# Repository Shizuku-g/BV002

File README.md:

# BV001

Design by nerdqaxeplus2(https://github.com/shufps/qaxe), change the ASIC to 1 x BM1373 AA (6.1TH/s SHA256)

Design tested and validated.  
Consume about 110 Watts on 12V for about 6.1TH/s (Vcore 1250mV, frequency 900Hz).  
Run at 735 MHz and 1140 mV, power wall around 78W, efficiency 14J/Th, 5TH/s.  
Use a 12V 15A PSU.

---

# BV002

**It is still an untested prototype! Don't build this expecting it to work at all.**

---

# BV003

**It is still an untested prototype! Don't build this expecting it to work at all.**

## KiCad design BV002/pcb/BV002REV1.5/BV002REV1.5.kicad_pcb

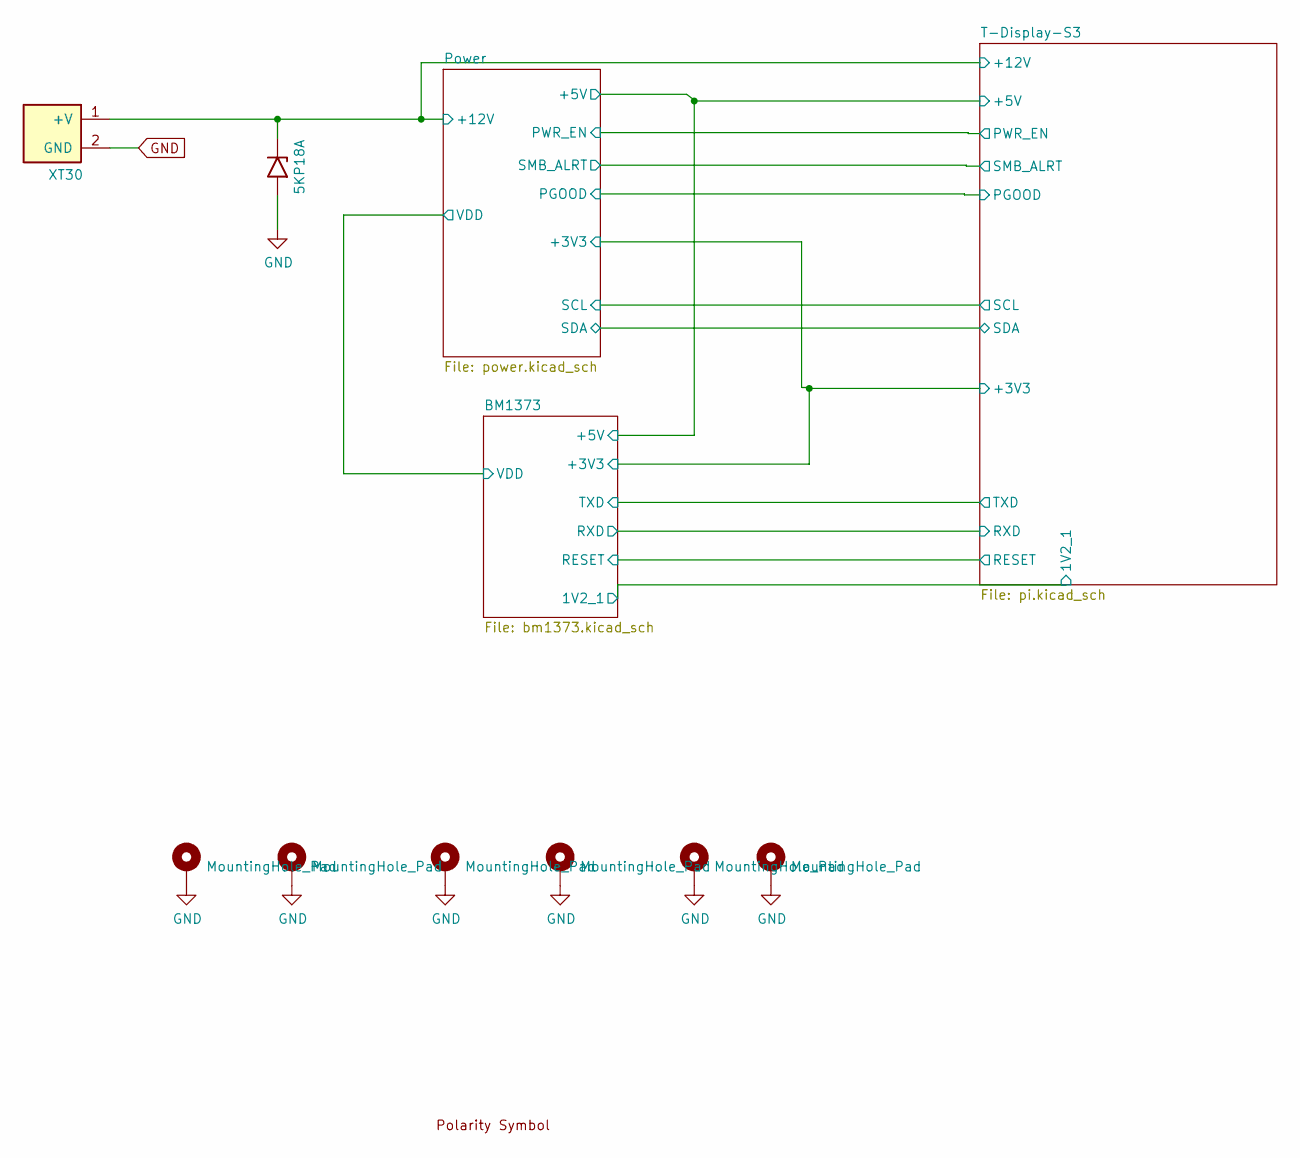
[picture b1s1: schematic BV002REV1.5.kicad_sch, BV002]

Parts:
D1: 5KP18A; D_SMB; PARTNO SMBJ12A; LCSC C3001973
H1, H2, H3, H4, H5, H6: MountingHole_Pad; MountingHole_3.2mm_M3_Pad_Via
J1: XT30; XT30PW-M; PARTNO XT30PW-M; LCSC C431092
U1: polarity

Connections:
+12V: D1.1 (A1), J1.1 (+V); also elsewhere on the board

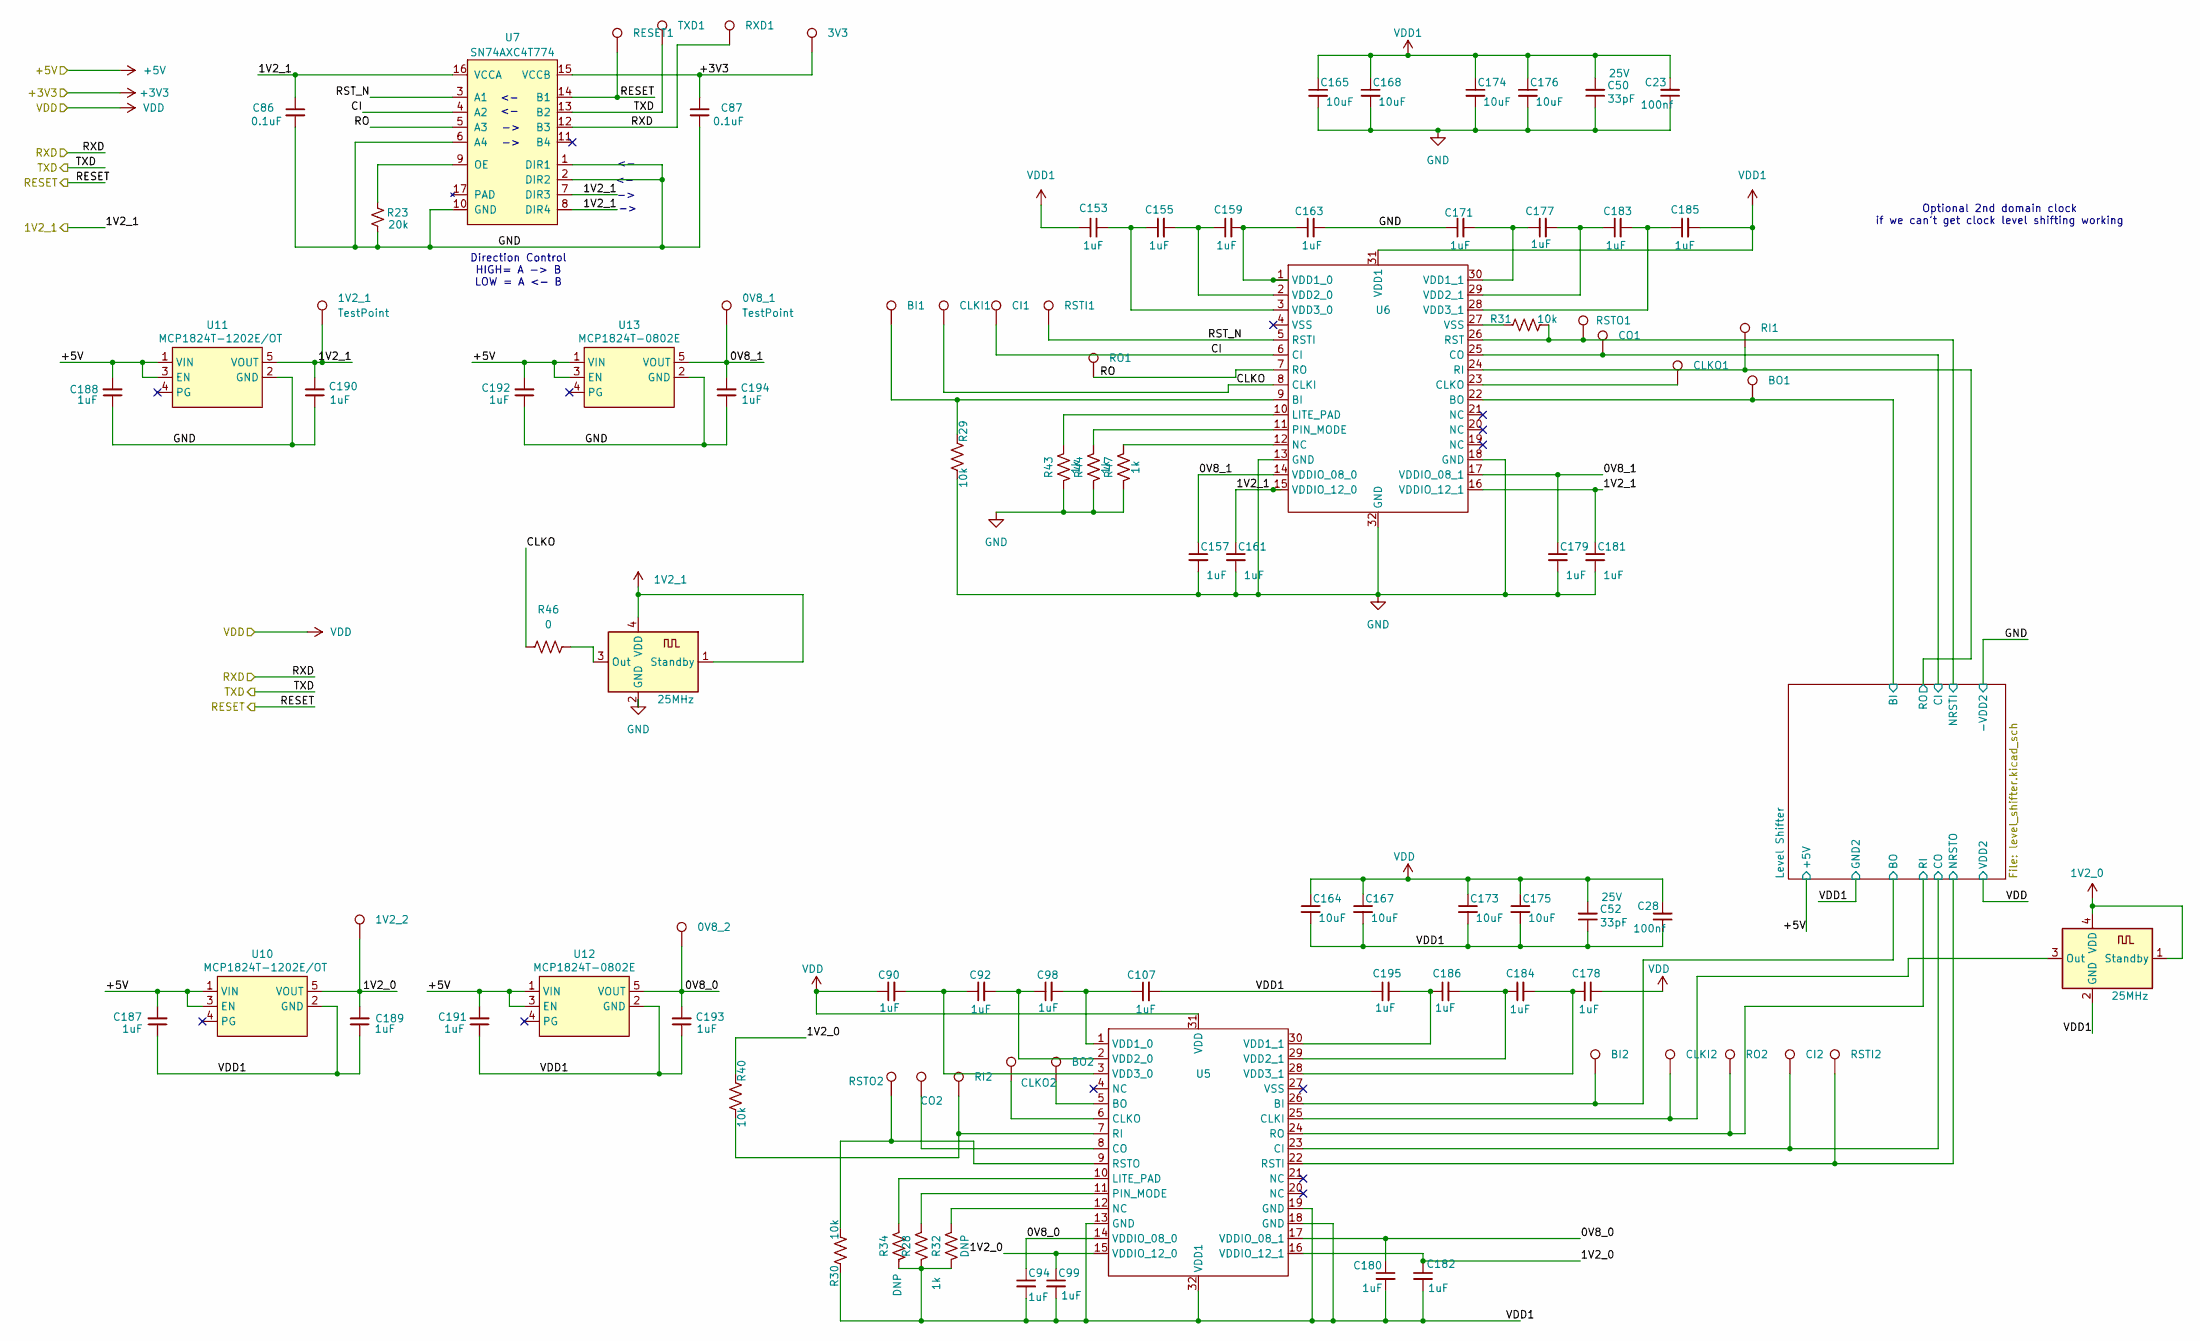
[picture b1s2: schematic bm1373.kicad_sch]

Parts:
0V8_1, 1V2_1: TestPoint; TestPoint_Pad_D1.5mm
0V8_2, 1V2_2, 3V3: TestPoint_Pad_D1.5mm
BI1, BI2: TestPoint_Pad_D1.5mm
BO1, BO2: TestPoint_Pad_D1.5mm
C23, C28: 100nf; C_0402_1005Metric; PARTNO GRM188R61E106KA73D
C50, C52: 33pF; C_0402_1005Metric; Voltage 25V; PARTNO KGM05ACG1E330JH
C86, C87: 0.1uF; C_0402_1005Metric; PARTNO KGM05AR71C104KH
C90, C92, C94, C98, C99, C107, C153, C155, C157, C159, C161, C163, C171, C177, C178, C179, C180, C181, C182, C183, C184, C185, C186, C195: 1uF; C_0402_1005Metric; PARTNO CL05A105KO5NNNC; LCSC C29266
C164, C165, C167, C168, C173, C174, C175, C176: 10uF; C_0603_1608Metric; PARTNO CL10A106MO8NQNC; LCSC C92487 Hot
C187, C188, C189, C190, C191, C192, C193, C194: 1uF; C_0402_1005Metric; PARTNO EMK105BJ105MV-F
CI1, CI2: TestPoint_Pad_D1.5mm
CLKI1, CLKI2: TestPoint_Pad_D1.5mm
CLKO1, CLKO2: TestPoint_Pad_D1.5mm
CO1, CO2: TestPoint_Pad_D1.5mm
R23: 20k; R_0402_1005Metric; PARTNO RC0402FR-0720KL
R28, R43, R44, R47: 1k; R_0402_1005Metric; PARTNO RC0402FR-071KL; LCSC C106235
R29, R30, R31, R40: 10k; R_0402_1005Metric; PARTNO RC0402DR-0710KL; LCSC C471764
R32, R34: DNP; R_0402_1005Metric; PARTNO RC0402FR-071KL; LCSC C106235
R46: 0; R_0402_1005Metric; PARTNO RC0402JR-070RL
RESET1: TestPoint_Pad_D1.5mm
RI1, RI2: TestPoint_Pad_D1.5mm
RO1, RO2: TestPoint_Pad_D1.5mm
RSTI1, RSTI2: TestPoint_Pad_D1.5mm
RSTO1, RSTO2: TestPoint_Pad_D1.5mm
RXD1: TestPoint_Pad_D1.5mm
TXD1: TestPoint_Pad_D1.5mm
U5, U6: B1373CC
U7: SN74AXC4T774; TSSOP-16_4.4x5mm_P0.65mm; PARTNO SN74AXC4T774BQBR
U8, U9: 25MHz; Oscillator_SMD_EuroQuartz_XO32-4Pin_3.2x2.5mm; PARTNO SX3M25.000E20F30THN
U10, U11: MCP1824T-1202E/OT; SOT-23-5; PARTNO MCP1824T-1202E/OT
U12, U13: MCP1824T-0802E; SOT-23-5; PARTNO MCP1824T-0802E/OT

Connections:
1V2_0: 1V2_2.1, C99.1, C182.1, C189.2, R40.1, U5.15 (VDDIO_12_0), U5.16 (VDDIO_12_1), U8.1 (Standby), U8.4 (VDD), U10.5 (VOUT)
1V2_1: 1V2_1.1, C86.1, C161.1, C181.1, C190.2, U6.15 (VDDIO_12_0), U6.16 (VDDIO_12_1), U7.7 (DIR3), U7.8 (DIR4), U7.16 (VCCA), U9.1 (Standby), U9.4 (VDD), U11.5 (VOUT); also elsewhere on the board
+5V: C187.2, C188.2, C191.2, C192.2, U10.1 (VIN), U10.3 (EN), U11.1 (VIN), U11.3 (EN), U12.1 (VIN), U12.3 (EN), U13.1 (VIN), U13.3 (EN); also elsewhere on the board
/BM1373/0V8_0: 0V8_2.1, C94.1, C180.1, C193.2, U5.14 (VDDIO_08_0), U5.17 (VDDIO_08_1), U12.5 (VOUT)
/BM1373/0V8_1: 0V8_1.1, C157.1, C179.1, C194.2, U6.14 (VDDIO_08_0), U6.17 (VDDIO_08_1), U13.5 (VOUT)
/BM1373/CI: CI1.1 (1_1), U6.6 (CI), U7.4 (A2)
/BM1373/CLKO: CLKI1.1 (1_1), R46.1, U6.8 (CLKI)
/BM1373/Level Shifter/BI: BO1.1 (1_1), U6.22 (BO); also elsewhere on the board
/BM1373/Level Shifter/BI2: BI2.1 (1_1), U5.26 (BI); also elsewhere on the board
/BM1373/Level Shifter/CI: CO1.1 (1_1), U6.25 (CO); also elsewhere on the board
/BM1373/Level Shifter/CI2: CI2.1 (1_1), U5.23 (CI); also elsewhere on the board
/BM1373/Level Shifter/NRSTI: R31.2, RSTO1.1 (1_1), U6.26 (RST); also elsewhere on the board
/BM1373/Level Shifter/NRSTI2: RSTI2.1 (1_1), U5.22 (RSTI); also elsewhere on the board
/BM1373/Level Shifter/RO: RI1.1 (1_1), U6.24 (RI); also elsewhere on the board
/BM1373/Level Shifter/RO2: RO2.1 (1_1), U5.24 (RO); also elsewhere on the board
/BM1373/RESET: RESET1.1 (1_1), U7.14 (B1); also elsewhere on the board
/BM1373/RO: RO1.1 (1_1), U6.7 (RO), U7.5 (A3)
/BM1373/RST_N: RSTI1.1 (1_1), U6.5 (RSTI), U7.3 (A1)
/BM1373/RXD: RXD1.1 (1_1), U7.12 (B3); also elsewhere on the board
/BM1373/TXD: TXD1.1 (1_1), U7.13 (B2); also elsewhere on the board
unnamed: R31.1, U6.27 (VSS)
unnamed: R32.1, U5.12 (NC)
unnamed: R47.1, U6.12 (NC)
unnamed: BO2.1 (1_1), U5.5 (BO)
unnamed: CLKI2.1 (1_1), U5.25 (CLKI), U8.3 (Out)
unnamed: CLKO2.1 (1_1), U5.6 (CLKO)
unnamed: CO2.1 (1_1), U5.8 (CO)
unnamed: R34.1, U5.10 (LITE_PAD)
unnamed: R28.1, U5.11 (PIN_MODE)
unnamed: R40.2, RI2.1 (1_1), U5.7 (RI)
unnamed: R30.2, RSTO2.1 (1_1), U5.9 (RSTO)
unnamed: C98.2, C107.1, U5.1 (VDD1_0)
unnamed: C186.1, C195.2, U5.30 (VDD1_1)
unnamed: C92.2, C98.1, U5.2 (VDD2_0)
unnamed: C184.1, C186.2, U5.29 (VDD2_1)
unnamed: C90.2, C92.1, U5.3 (VDD3_0)
unnamed: C178.1, C184.2, U5.28 (VDD3_1)
unnamed: BI1.1 (1_1), R29.1, U6.9 (BI)
unnamed: CLKO1.1 (1_1), U6.23 (CLKO)
unnamed: R43.1, U6.10 (LITE_PAD)
unnamed: R44.1, U6.11 (PIN_MODE)
unnamed: C159.2, C163.1, U6.1 (VDD1_0)
unnamed: C171.2, C177.1, U6.30 (VDD1_1)
unnamed: C155.2, C159.1, U6.2 (VDD2_0)
unnamed: C177.2, C183.1, U6.29 (VDD2_1)
unnamed: C153.2, C155.1, U6.3 (VDD3_0)
unnamed: C183.2, C185.1, U6.28 (VDD3_1)
unnamed: R23.2, U7.9 (OE)
unnamed: R46.2, U9.3 (Out)
VDD: C28.2, C52.2, C90.1, C164.1, C167.1, C173.1, C175.1, C178.2, U5.31 (VDD); also elsewhere on the board
VDD1: C23.2, C28.1, C50.2, C52.1, C94.2, C99.2, C107.2, C153.1, C164.2, C165.1, C167.2, C168.1, C173.2, C174.1, C175.2, C176.1, C180.2, C182.2, C185.2, C187.1, C189.1, C191.1, C193.1, C195.1, R28.2, R30.1, R32.2, R34.2, U5.13 (GND), U5.18 (GND), U5.19 (GND), U5.32 (VDD1), U6.31 (VDD1), U8.2 (GND), U10.2 (GND), U12.2 (GND); also elsewhere on the board

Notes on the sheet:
Optional 2nd domain clock if we can't get clock level shifting working
Direction Control HIGH= A -> B LOW = A <- B

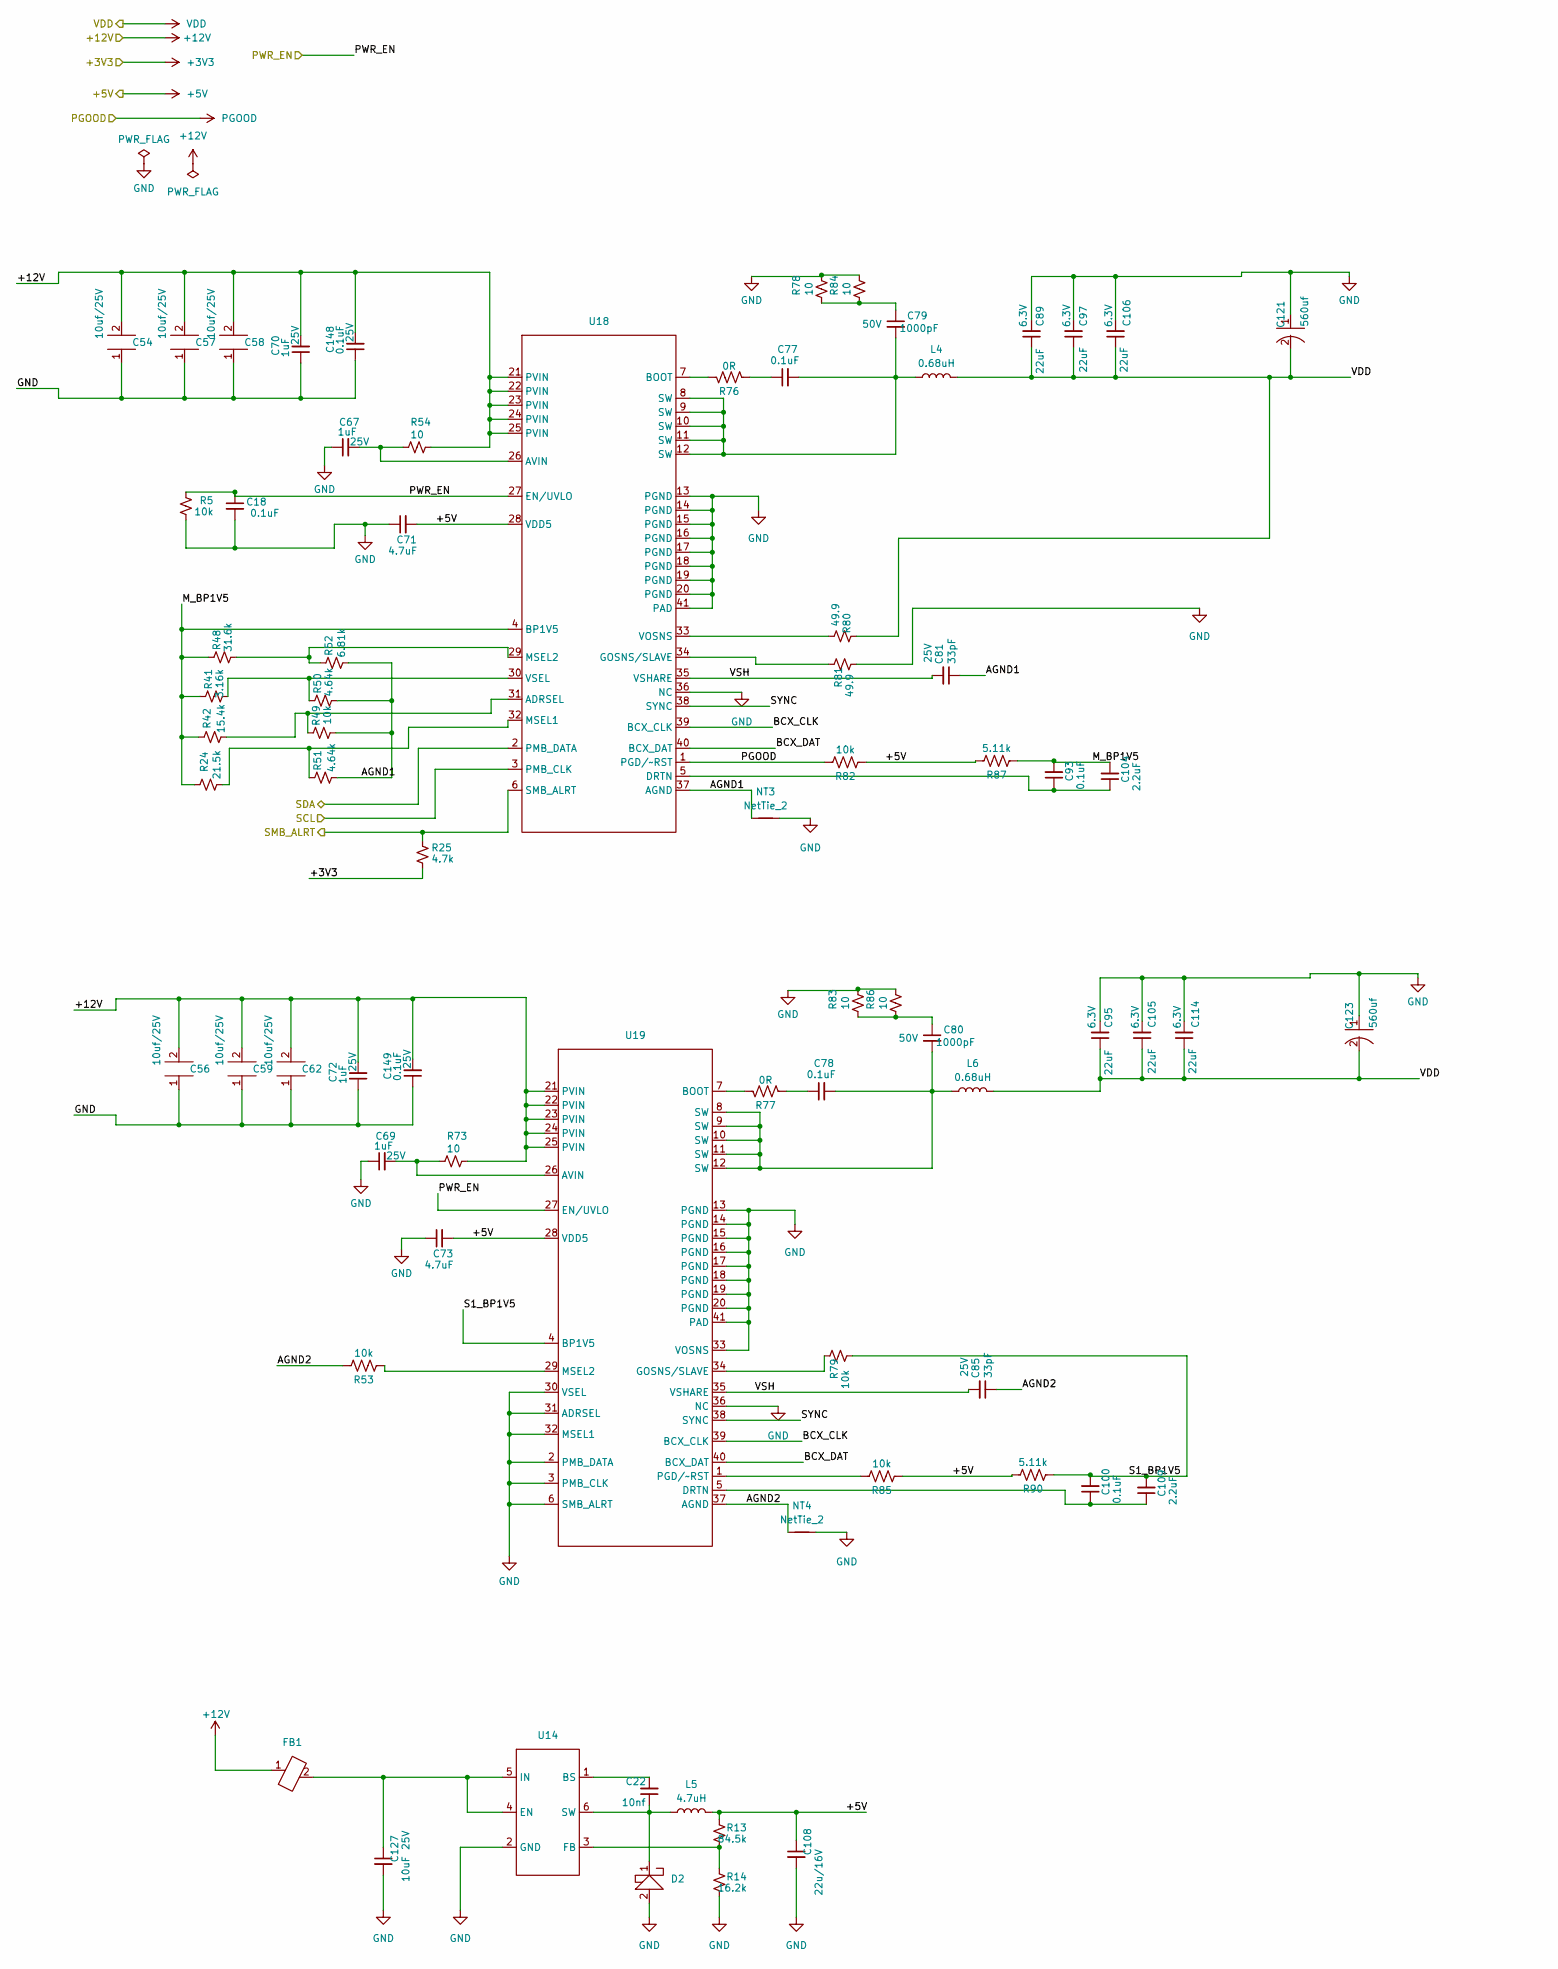
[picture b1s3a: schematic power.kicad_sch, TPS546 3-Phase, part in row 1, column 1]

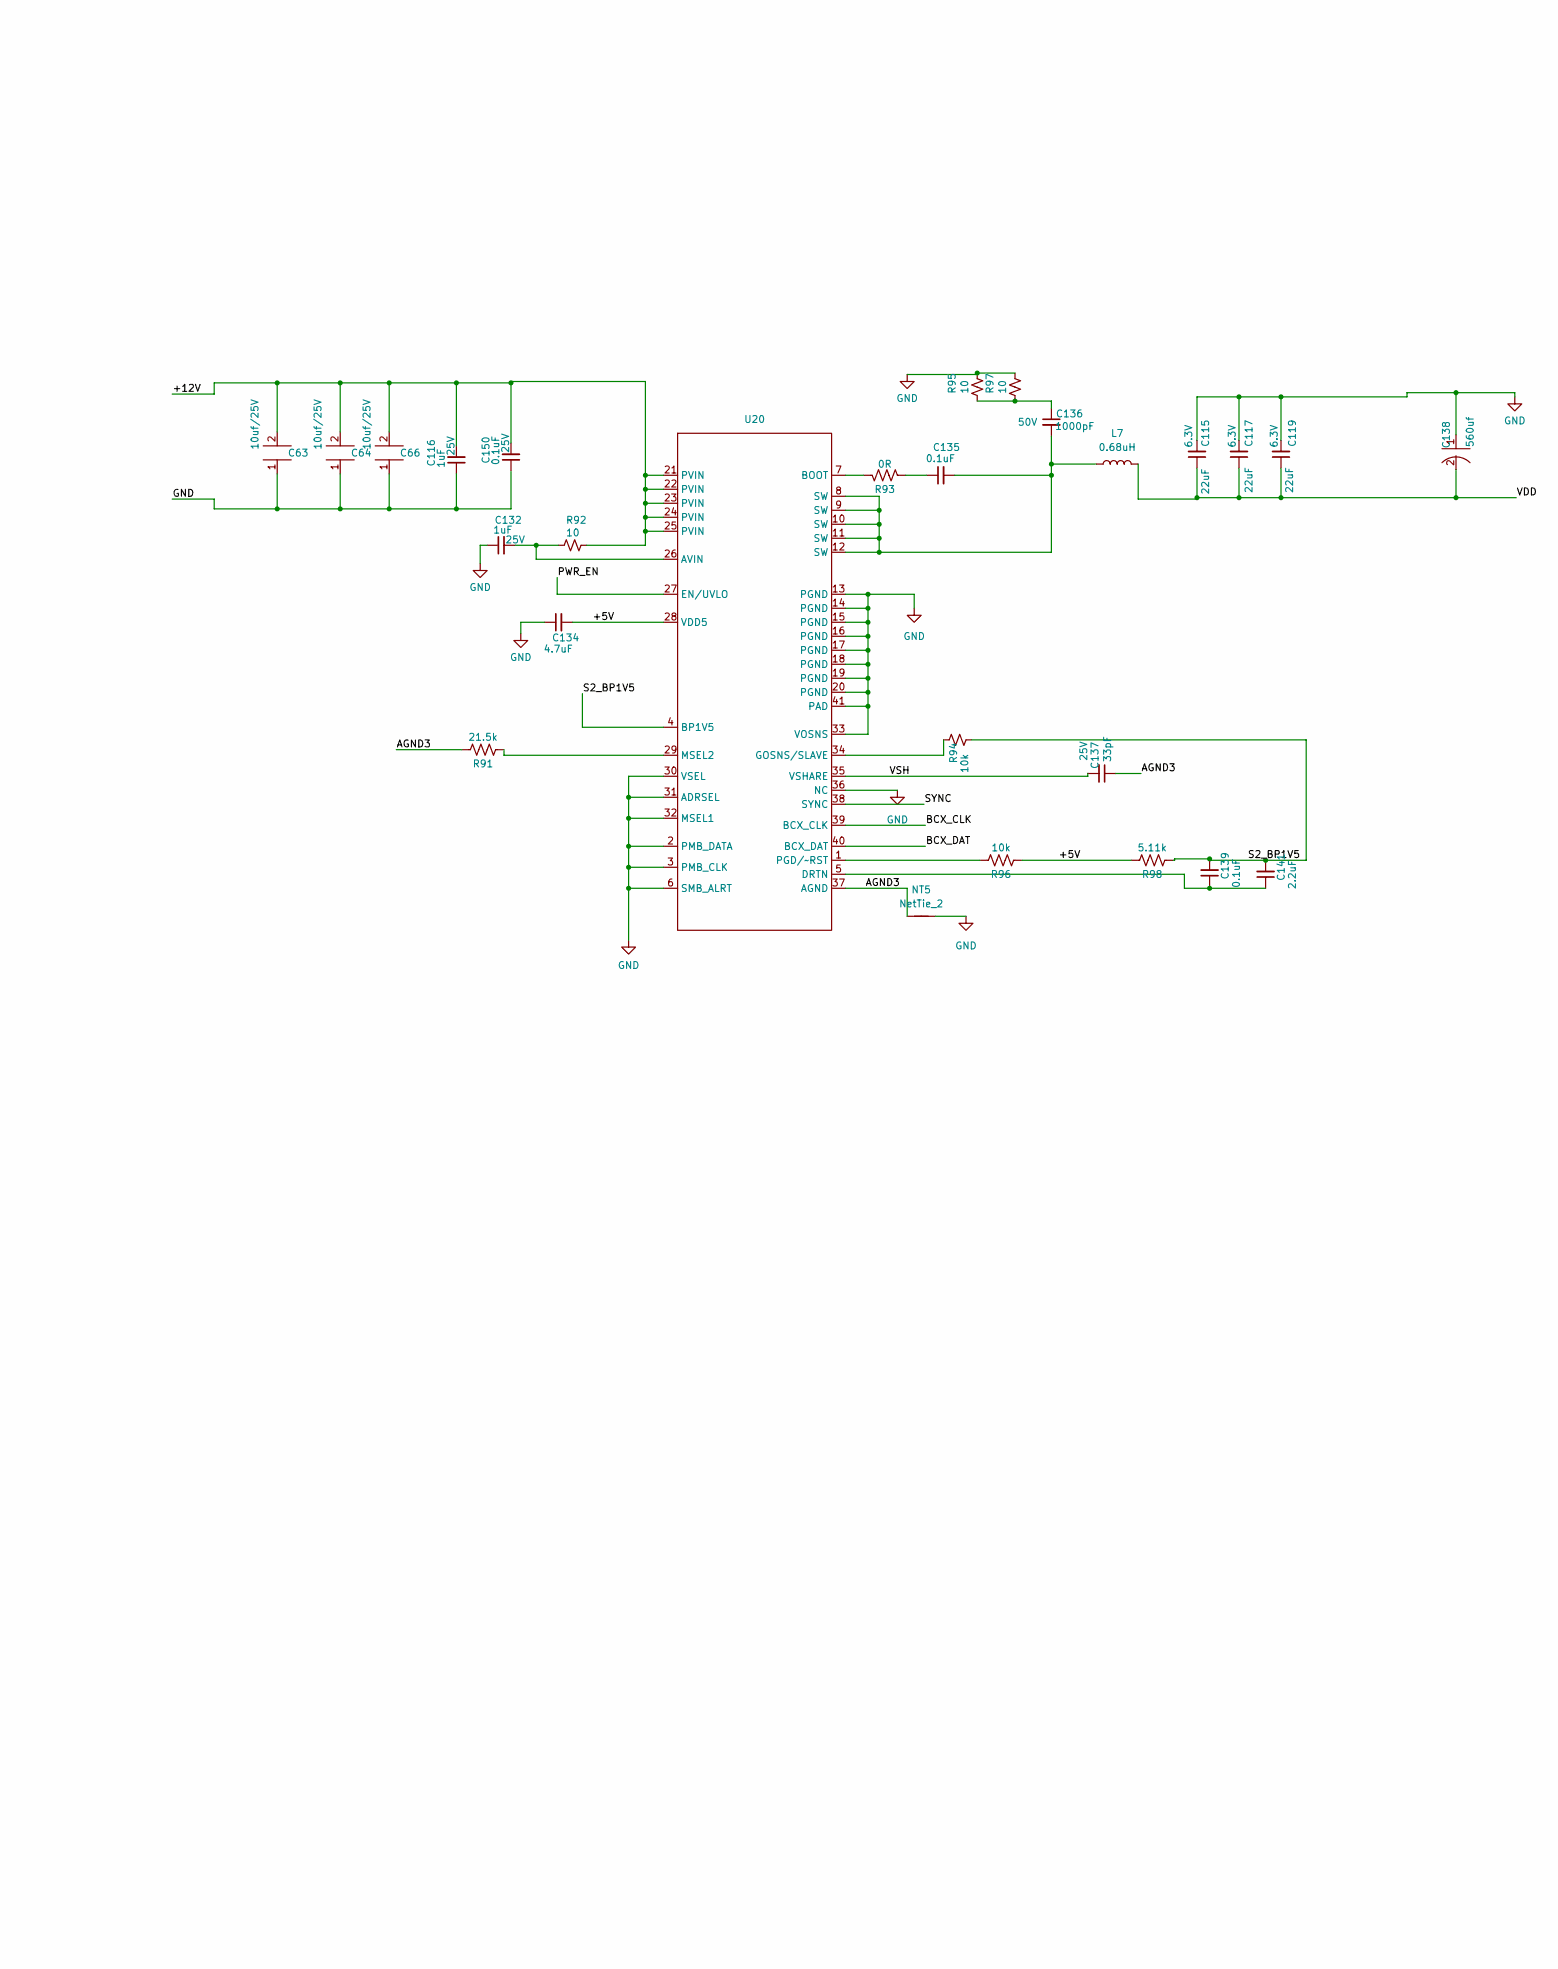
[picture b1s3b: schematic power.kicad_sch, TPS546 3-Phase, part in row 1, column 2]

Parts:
C18, C77, C78, C135: 0.1uF; C_0402_1005Metric; PARTNO KGM05AR71C104KH
C22: 10nf; C_0402_1005Metric; PARTNO GRM188R61E106KA73D
C54, C56, C57, C58, C59, C62, C63, C64, C66: 10uf/25V; C_0805_2012Metric
C67, C69, C70, C72, C116, C132: 1uF; C_0402_1005Metric; Voltage 25V; PARTNO TMK107B7105KA-T
C71, C73, C134: 4.7uF; C_0402_1005Metric; PARTNO GRM155R61A475MEAAD
C79, C80, C136: 1000pF; C_0402_1005Metric; Voltage 50V; PARTNO CC0402JRNPO9BN101
C81, C85, C137: 33pF; C_0402_1005Metric; Voltage 25V; PARTNO KGM05ACG1E330JH
C89, C95, C97, C105, C106, C114, C115, C117, C119: 22uF; C_1206_3216Metric; Voltage 6.3V; PARTNO CL31A107MQHNNNE
C93, C100, C139: 0.1uF; C_0402_1005Metric; PARTNO GRM155R61A475MEAAD
C104, C109, C141: 2.2uF; C_0402_1005Metric; PARTNO GRM155R61A475MEAAD
C108: 22u/16V; C_0603_1608Metric; PARTNO GRM188R61E106KA73D
C121, C123, C138: 560uf; D7.3xL4.3
C127: 10uF; C_0603_1608Metric; Voltage 25V; PARTNO GRM188R61E106KA73D
C148, C149, C150: 0.1uF; C_0402_1005Metric; Voltage 25V; PARTNO TMK107B7105KA-T
D2: D_SOD-128
FB1: FB0603
L4, L6, L7: 0.68uH; SLC1175-271MEC_COC; PARTNO SLC1175-301
L5: 4.7uH; L_Ferrocore_DLG-0703; PARTNO FTC201612S1R5MBCA
NT3, NT4, NT5: NetTie_2; NetTie-2_SMD_Pad0.2mmx1mm
R5, R49: 10k; R_0402_1005Metric; PARTNO RC0402JR-0710KL
R13: 84.5k; R_0402_1005Metric; PARTNO RC0402FR-0752K3L
R14: 16.2k; R_0402_1005Metric; PARTNO RC0402FR-0752K3L
R24: 21.5k; R_0402_1005Metric; PARTNO RC0402JR-0710KL
R25: 4.7k; R_0402_1005Metric; PARTNO RC0402JR-074K7L
R41: 3.16k; R_0402_1005Metric; PARTNO RC0402JR-0710KL
R42: 15.4k; R_0402_1005Metric; PARTNO RC0402JR-0710KL
R48: 31.6k; R_0402_1005Metric; PARTNO RC0402JR-0710KL
R50, R51: 4.64k; R_0402_1005Metric; PARTNO RC0402JR-0710KL
R52: 6.81k; R_0402_1005Metric; PARTNO RC0402JR-0710KL
R53, R82, R85, R96: 10k; R_0402_1005Metric; PARTNO RC0402DR-0710KL; LCSC C471764
R54, R73, R78, R83, R84, R86, R92, R95, R97: 10; R_0402_1005Metric; PARTNO RC0402FR-0710RL
R76, R77, R93: 0R; R_0402_1005Metric; PARTNO RC0402FR-071KL; LCSC C106235
R79, R94: 10k; R_0402_1005Metric; PARTNO RC0402FR-0749R9L
R80, R81: 49.9; R_0402_1005Metric; PARTNO RC0402FR-0749R9L
R87, R90, R98: 5.11k; R_0402_1005Metric; PARTNO RC0402DR-0710KL; LCSC C471764
R91: 21.5k; R_0402_1005Metric; PARTNO RC0402DR-0710KL; LCSC C471764
U14: SOT-23-6
U18, U19, U20: LQFN40-CLIP

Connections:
+5V: C71.2, C73.2, C108.1, C134.2, L5.2, R13.2, R82.1, R85.1, R87.2, R90.2, R96.1, R98.2, U18.28 (VDD5), U19.28 (VDD5), U20.28 (VDD5); also elsewhere on the board
+12V: C54.2, C56.2, C57.2, C58.2, C59.2, C62.2, C63.2, C64.2, C66.2, C70.2, C72.2, C116.2, C148.2, C149.2, C150.2, FB1.1, R54.1, R73.1, R92.1, U18.21 (PVIN), U18.22 (PVIN), U18.23 (PVIN), U18.24 (PVIN), U18.25 (PVIN), U19.21 (PVIN), U19.22 (PVIN), U19.23 (PVIN), U19.24 (PVIN), U19.25 (PVIN), U20.21 (PVIN), U20.22 (PVIN), U20.23 (PVIN), U20.24 (PVIN), U20.25 (PVIN); also elsewhere on the board
/T-Display-S3/SCL: U18.3 (PMB_CLK); also elsewhere on the board
/T-Display-S3/SDA: U18.2 (PMB_DATA); also elsewhere on the board
/T-Display-S3/SMB_ALRT: R25.1, U18.6 (SMB_ALRT); also elsewhere on the board
/power1/AGND1: C81.1, NT3.2, R49.1, R50.1, R51.1, R52.1, U18.37 (AGND)
/power1/AGND2: C85.1, NT4.2, R53.2, U19.37 (AGND)
/power1/AGND3: C137.1, NT5.2, R91.2, U20.37 (AGND)
/power1/BCX_CLK: U18.39 (BCX_CLK), U19.39 (BCX_CLK), U20.39 (BCX_CLK)
/power1/BCX_DAT: U18.40 (BCX_DAT), U19.40 (BCX_DAT), U20.40 (BCX_DAT)
/power1/M_BP1V5: C93.2, C104.2, R24.2, R41.2, R42.2, R48.2, R87.1, U18.4 (BP1V5)
/power1/PWR_EN: C18.1, R5.2, U18.27 (EN/UVLO), U19.27 (EN/UVLO), U20.27 (EN/UVLO); also elsewhere on the board
/power1/S1_BP1V5: C100.2, C109.2, R79.2, R90.1, U19.4 (BP1V5)
/power1/S2_BP1V5: C139.2, C141.2, R94.2, R98.1, U20.4 (BP1V5)
/power1/SYNC: U18.38 (SYNC), U19.38 (SYNC), U20.38 (SYNC)
/power1/VSH: C81.2, C85.2, C137.2, U18.35 (VSHARE), U19.35 (VSHARE), U20.35 (VSHARE)
unnamed: C77.1, R76.2
unnamed: C77.2, C79.2, L4.1, U18.8 (SW), U18.9 (SW), U18.10 (SW), U18.11 (SW), U18.12 (SW)
unnamed: C78.1, R77.2
unnamed: C78.2, C80.2, L6.1, U19.8 (SW), U19.9 (SW), U19.10 (SW), U19.11 (SW), U19.12 (SW)
unnamed: C79.1, R78.2, R84.2
unnamed: C80.1, R83.2, R86.2
unnamed: C135.1, R93.2
unnamed: C135.2, C136.2, L7.1, U20.8 (SW), U20.9 (SW), U20.10 (SW), U20.11 (SW), U20.12 (SW)
unnamed: C136.1, R95.2, R97.2
unnamed: C22.2, U14.1 (BS)
unnamed: C127.1, FB1.2, U14.4 (EN), U14.5 (IN)
unnamed: R13.1, R14.2, U14.3 (FB)
unnamed: C22.1, D2.1, L5.1, U14.6 (SW)
unnamed: R42.1, R49.2, U18.31 (ADRSEL)
unnamed: C67.2, R54.2, U18.26 (AVIN)
unnamed: R76.1, U18.7 (BOOT)
unnamed: C93.1, C104.1, U18.5 (DRTN)
unnamed: R81.1, U18.34 (GOSNS/SLAVE)
unnamed: R24.1, R51.2, U18.32 (MSEL1)
unnamed: R48.1, R52.2, U18.29 (MSEL2)
unnamed: R80.2, U18.33 (VOSNS)
unnamed: R41.1, R50.2, U18.30 (VSEL)
unnamed: C69.2, R73.2, U19.26 (AVIN)
unnamed: R77.1, U19.7 (BOOT)
unnamed: C100.1, C109.1, U19.5 (DRTN)
unnamed: R79.1, U19.34 (GOSNS/SLAVE)
unnamed: R53.1, U19.29 (MSEL2)
unnamed: R85.2, U19.1 (PGD/~RST)
unnamed: C132.2, R92.2, U20.26 (AVIN)
unnamed: R93.1, U20.7 (BOOT)
unnamed: C139.1, C141.1, U20.5 (DRTN)
unnamed: R94.1, U20.34 (GOSNS/SLAVE)
unnamed: R91.1, U20.29 (MSEL2)
unnamed: R96.2, U20.1 (PGD/~RST)
PGOOD: R82.2, U18.1 (PGD/~RST); also elsewhere on the board
VDD: C89.1, C95.1, C97.1, C105.1, C106.1, C114.1, C115.1, C117.1, C119.1, C121.2, C123.2, C138.2, L4.2, L6.2, L7.2, R80.1; also elsewhere on the board

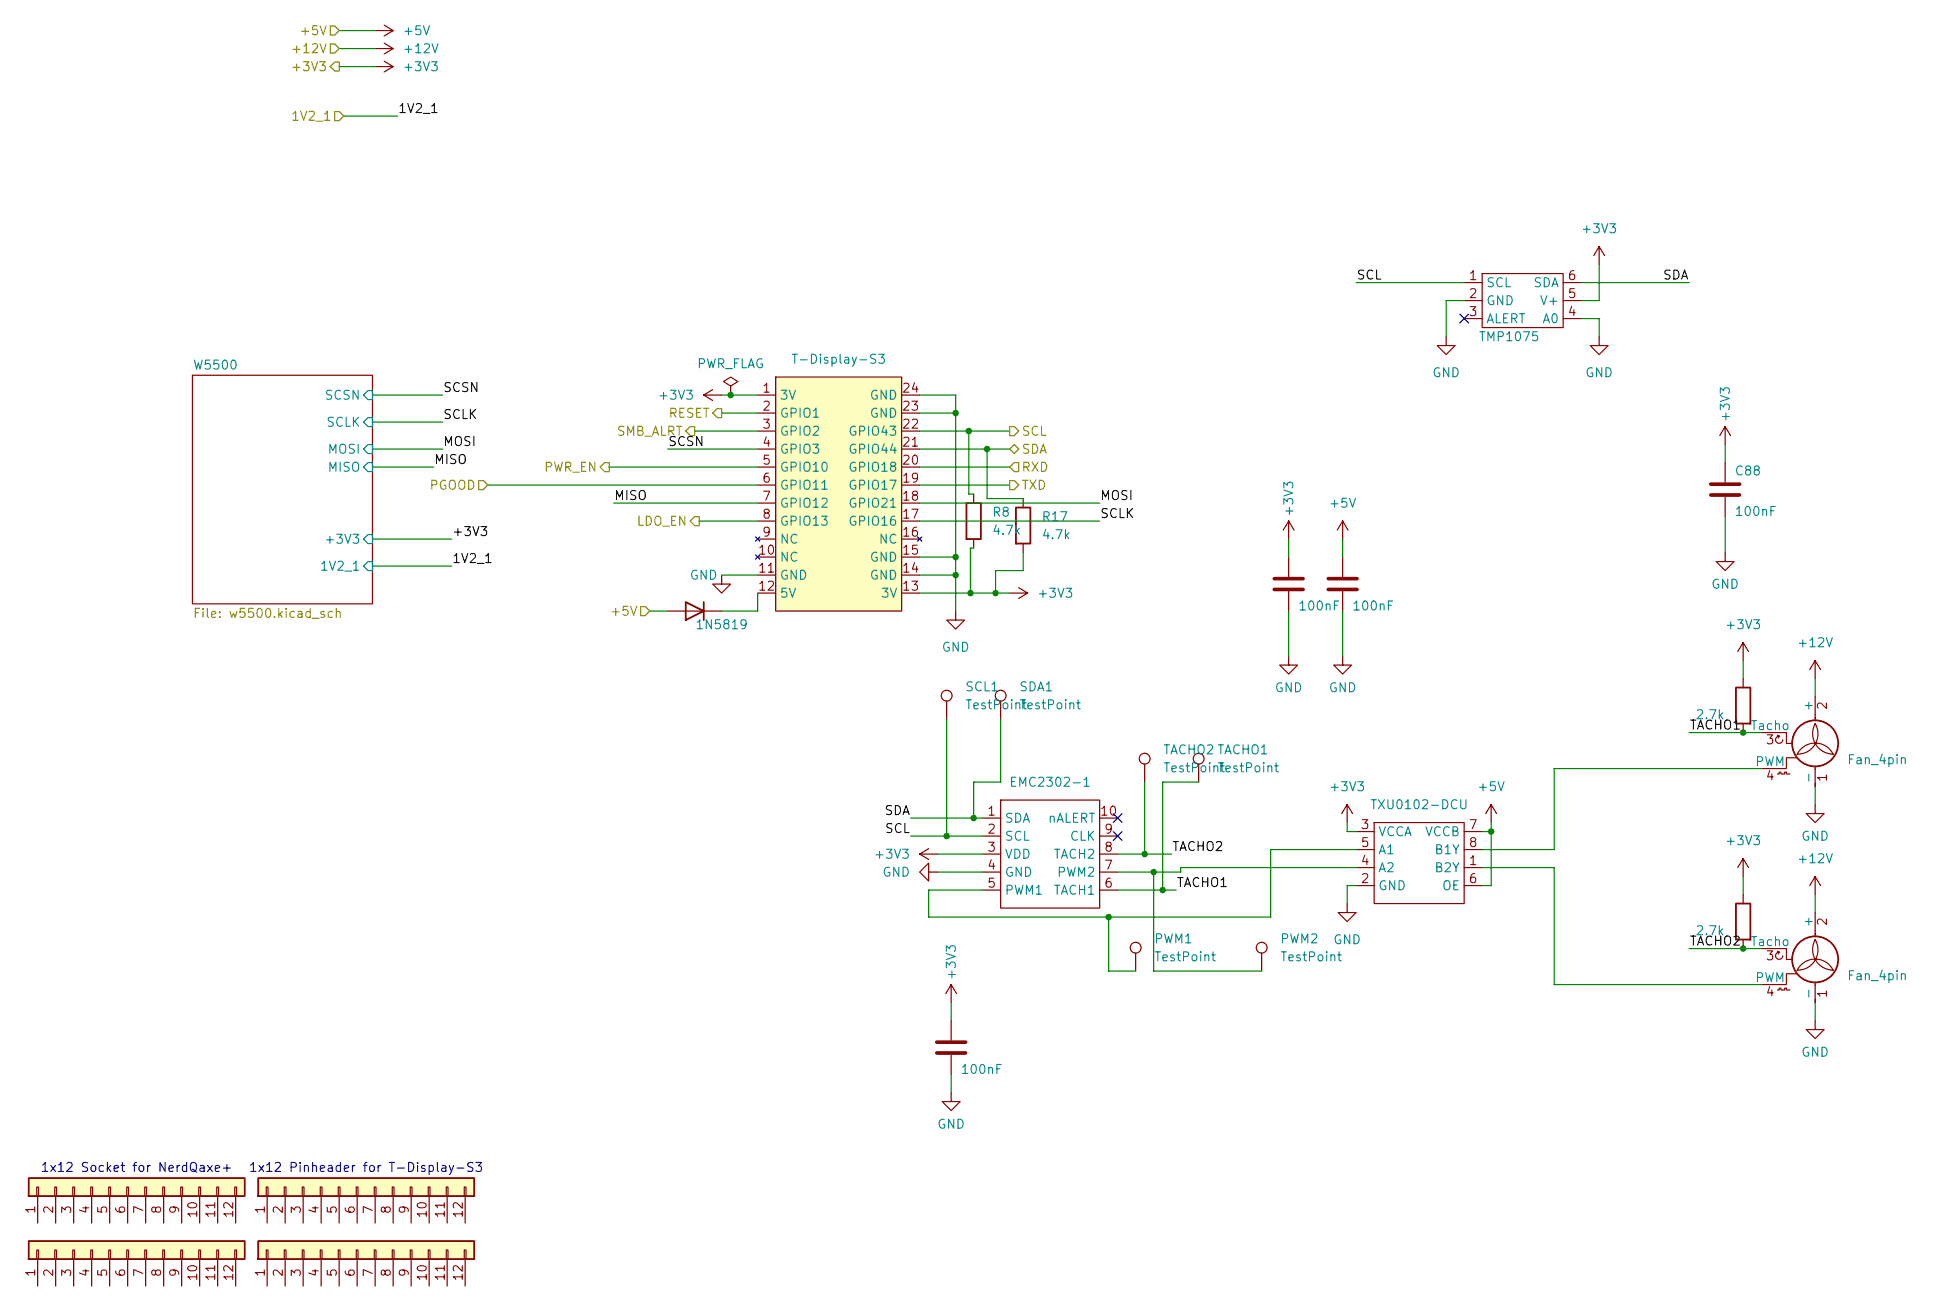
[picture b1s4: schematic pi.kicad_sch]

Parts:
C88, C96, C102, C103: 100nF; C_0402_1005Metric; PARTNO CC0402KRX7R7BB104; LCSC C60474
D3: 1N5819; D_SOD-123; PARTNO 1N5819HWQ-7-F
J5, J6: Conn_01x12-Socket; PARTNO 61301211821
J7, J8: Conn_01x12-Header
M1, M2: Fan_4pin; FanPinHeader_1x04_P2.54mm_Vertical; PARTNO 0470531000
PWM1, PWM2: TestPoint; TestPoint_Pad_D1.5mm
R8, R17: 4.7k; R_0402_1005Metric
R33, R35: 2.7k; R_0402_1005Metric; PARTNO RC0402FR-072K7L; LCSC C138017
SCL1: TestPoint; TestPoint_Pad_D1.5mm
SDA1: TestPoint; TestPoint_Pad_D1.5mm
TACHO1, TACHO2: TestPoint; TestPoint_Pad_D1.5mm
U30: T-Display-S3
U32: EMC2302-1; MSOP-10_3x3mm_P0.5mm; PARTNO EMC2302-1-AIZL-TR
U33: TXU0102-DCU; VSSOP-8_2.3x2mm_P0.5mm; PARTNO TXU0102DCUR
U37: TMP1075; TMP1075-DRL; PARTNO TMP1075NDRLR

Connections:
+5V: C96.1, D3.2 (A), U33.6 (OE), U33.7 (VCCB); also elsewhere on the board
+12V: M1.2 (+), M2.2 (+); also elsewhere on the board
/BM1373/RESET: U30.2 (GPIO1); also elsewhere on the board
/BM1373/RXD: U30.20 (GPIO18); also elsewhere on the board
/BM1373/TXD: U30.19 (GPIO17); also elsewhere on the board
/T-Display-S3/LDO_EN: U30.8 (GPIO13)
/T-Display-S3/MISO: U30.7 (GPIO12); also elsewhere on the board
/T-Display-S3/MOSI: U30.18 (GPIO21); also elsewhere on the board
/T-Display-S3/SCL: R8.1, SCL1.1, U30.22 (GPIO43), U32.2 (SCL), U37.1 (SCL); also elsewhere on the board
/T-Display-S3/SCLK: U30.17 (GPIO16); also elsewhere on the board
/T-Display-S3/SCSN: U30.4 (GPIO3); also elsewhere on the board
/T-Display-S3/SDA: R17.1, SDA1.1, U30.21 (GPIO44), U32.1 (SDA), U37.6 (SDA); also elsewhere on the board
/T-Display-S3/SMB_ALRT: U30.3 (GPIO2); also elsewhere on the board
/T-Display-S3/TACHO1: M1.3 (Tacho), R33.2, TACHO1.1 (1_1), U32.6 (TACH1)
/T-Display-S3/TACHO2: M2.3 (Tacho), R35.2, TACHO2.1 (1_1), U32.8 (TACH2)
/power1/PWR_EN: U30.5 (GPIO10); also elsewhere on the board
unnamed: D3.1 (K), U30.12 (5V)
unnamed: M1.4 (PWM), U33.8 (B1Y)
unnamed: M2.4 (PWM), U33.1 (B2Y)
unnamed: PWM1.1 (1_1), U32.5 (PWM1), U33.5 (A1)
unnamed: PWM2.1 (1_1), U32.7 (PWM2), U33.4 (A2)
PGOOD: U30.6 (GPIO11); also elsewhere on the board

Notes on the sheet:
1x12 Socket for NerdQaxe+
1x12 Pinheader for T-Display-S3
